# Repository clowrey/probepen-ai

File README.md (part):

# ProbePen-AI

A USB-C pen-shaped two-channel oscilloscope built around an **RP2354B** and an **AD9288** dual 8-bit
ADC, with an IPS LCD on the underside, four side buttons, a 4-channel logic pod and a WAGO push-in
terminal at the nose for the two probe inputs. Everything (schematic, placement, routing,
fabrication files, case and firmware) is generated by scripts in this repository.

> **Status (2026-11-27):** re-laid out and fully routed on the `relayout` branch: KiCad DRC with
> schematic parity reports 0 errors and 0 unconnected items (the only warnings are the open ends of the
> In2 supply rails, by design), ERC is clean and all 149 offline tests pass. 2.5 m of track, 223 vias.
> About 160 mm of slow signals (gain-switch and DC-sense lines, two buttons, pod and LCD control) use
> the inner layers as jumpers, the longest 27 mm. The case fits the routed board, and the firmware
> has its full main loop and user interface (host-tested; not yet built against the Pico SDK).
> No board has been made or bench-tested yet.

**Try it in the browser: [ProbePen-AI simulator](https://clowrey.github.io/probepen-ai/).** The page runs the
firmware's own user interface (`firmware/src`, compiled to WebAssembly) on simulated probe signals. You
can press the side buttons, connect preset signals (UART, PWM, fast edges, glitches, over-range, a 12 V
rail, CAN FD, an SPI bus on the logic pod), and drive it from a host app over the real USB command
protocol: capture once or continuously (with a history to scroll back through), measure, calibrate, decode
UART and CAN FD buses into text, stream continuously (with a USB budget you can set, to see where samples start
to drop), take deep records, and receive ASK snapshots. A selector switches between the 150 MHz firmware and
the 250 MHz overclocked build. The simulated hardware is in [`sim/sim.c`](sim/sim.c). AI mode works only in a
local copy of the page (see [AI mode](#ai-mode)), since it needs an API key on your computer.

| | |
|---|---|
| **MCU** | RP2354B (QFN-80, 0.4 mm pitch): dual Cortex-M33 at 150 MHz (or overclocked to 250 MHz, a build option), 2 MB stacked flash, 12 PIO state machines, on-chip 1.1 V core buck (layout copied from the owner's CellKeeper board), 12 MHz Abracon ABM8-272-T3 crystal (the one Raspberry Pi tuned the Pico 2 for: ESR ≤ 50 Ω, 15 pF load caps, 1 kΩ on XOUT) |
| **Scope ADC** | AD9288 (LQFP-48, hand-soldered, not placed by the assembler): two 8-bit channels, read by one PIO program as one 32-bit word per sample, clocked by PIO side-set at up to 75 MSPS (150 MHz / 2 / integer divider, set by the timebase), or 125 MSPS in the 250 MHz build |
| **Front end** | Per channel: 940 kΩ (2 × 470 kΩ, each bridged by 2.2 pF: 1.1 pF in all, 100 V) into a 100 kΩ / 51 kΩ divider biased from the 3.000 V reference (rests at 0.978 V), BAV199 clamp, RS8752 buffer, RS8752 inverting gain stage pivoting on REF_MID (0.978 V), 74LVC2G66 gain switch. High range about ±5 V, low range about ±26 V |
| **References and supplies** | REF3030 (3.000 V), two RT9013-33 LDOs (`+3V3_DIG`, and `+3V3_ANA` behind a 600 Ω ferrite); the analog ground island joins digital ground at one 0 Ω link (R16) |
| **Logic pod** | 6-pin JST-SH side connector on GPIO0..3 (the 5 V tolerant pins, while the pen is powered), 1 kΩ in each line, PTC-fused 3.3 V out, SRV05-4 ESD with its VP pin open (tied to VBUS, a live target would power the unplugged pen through it) |
| **Display and buttons** | 1.14" 135 × 240 ST7789V IPS LCD (Wisevision N114-2413THBIG01-H13, LCSC C2890618), its 13-pin 0.7 mm flex soldered to pads on the bottom side (SPI1), AO3401A backlight switch; four side-actuated buttons (ASK, MODE/BOOTSEL, UP, DOWN); two front white work-light LEDs |
| **Board** | 132 × 17.6 mm, tapered to 14 mm at the nose, 4 layers (JLC04161H-7628), 1.6 mm, single-sided assembly on the top |
| **Case** | Two-piece build123d pen shell, 136 × 21.5 × 12.2 mm; screws self-tap into the plastic (no inserts) |

## Scope specifications

These figures come from the circuit values, the datasheets and the firmware as it is written today
(`firmware/src/app.c`, `main.c`). No board has been measured yet. Rows marked *possible* need a
firmware change but no hardware change.

| | |
|---|---|
| **Channels** | 2, sampled at the same instant (both AD9288 encode pins are driven from one MCU clock pin) |
| **Resolution** | 8 bits. One step is 39 mV on the ±5 V range and 214 mV on the ±26 V range |
| **Ranges** | ±5.0 V (high gain) and about ±26 V (low gain), chosen per channel, automatically or fixed. Auto-range switches up at 90 % of ±5 V or when the ADC reports over-range, and back down below 70 % |
| **Input** | About 975 kΩ, DC coupled. The divider is compensated: 1.1 pF over 22 pF, plus the clamp, buffer and pads (about 5 pF), plus an optional 2–10 pF trimmer (`CT1`/`CT2`, on the bottom). The trimmer only adds capacitance; fit it and set it for a flat square wave |
| **Bandwidth** | About 25 MHz expected: the 31 MHz anti-alias filter (51 Ω × 100 pF) in front of the ADC together with the gain stage's feedback pole (1.5 kΩ ∥ 2.2 pF, 48 MHz, on the ±5 V range; it was 23 MHz with 4.7 pF). The 250 MHz RS8752 amplifiers are not the limit. Not yet measured |
| **Maximum sample rate** | 75 MS/s on each channel at once (150 MHz system clock ÷ 2 PIO cycles per sample) |
| **Overclocked build** | `cmake -DPROBEPEN_SYS_MHZ=250`: the RP2354B at 250 MHz (core voltage raised to 1.20 V at boot) and the AD9288 at up to **125 MS/s** per channel, beyond the AD9288-80's 80 MS/s rating. Every rate in the firmware follows from the clock (`firmware/include/probepen_clock.h`): sample rates are 125 MHz ÷ an integer, peak detect runs at 4.2 MS/s, and bus decoding gets 5/3 the CPU time. Neither the core, the flash (its clock follows the system clock) nor the ADC has been run this fast on this board; the simulator has a build for each clock |
| **One channel faster?** | Not yet in firmware. Showing one channel does not raise the rate. The board gives channel B its own encode clock pin (GPIO28, `ADC_CLKB`), so a firmware mode can clock the two channels 180° apart and interleave them: **150 MS/s on one signal** (250 MS/s in the 250 MHz build), with both probe tips on the same point. Today the firmware clocks the two channels in phase. Interleaving doubles the sample density, not the bandwidth (the 31 MHz anti-alias filter stays), and needs the two channels' gain, offset and timing matched by calibration |
| **Sample rate per timebase** | At 150 MHz: 100 ns/div to 1 µs/div: 75 MS/s. 2 µs: 25 MS/s. 5 µs: 10.7 MS/s. 10 µs: 5 MS/s. 20 µs: 2.4 MS/s. All rates are 75 MHz ÷ an integer, so there is no clock jitter from fractional dividers |
| **Peak detect** | At 50 µs/div and slower, the ADC keeps running at 2.5 MS/s (4.2 MS/s at 250 MHz). Every 4 to 2048 samples are reduced to a minimum and a maximum, so pulses of 0.4 µs or longer still show at 50 ms/div |
| **Record length (screen)** | 4096 samples per channel per capture (16 KB DMA buffer). Each capture holds about 4 screen widths, used for the trigger search: 512 samples (6.8 µs) at 100 ns/div, 3000 samples (40 µs) at 1 µs/div, about 2000 samples at slower timebases (0.8 ms at 20 µs/div, 0.4 s at 10 ms/div), and 4096 samples (1.7 s) at 50 ms/div |
| **Deep record** | `DEEP n [ch] [rate]`: one long record at 75 MS/s, or 75 MS/s ÷ an integer: **196,608 samples per channel with both channels (2.62 ms at 75 MS/s), or 393,216 with one (5.24 ms)**. Two PIO state machines run in lockstep, one per 8-bit bus, so each sample takes 1 byte (the screen capture spends a 32-bit word per sample pair). The 384 KB buffer is shared with the stream ring, the capture ring and the LCD framebuffer, since only one of them runs at a time. The firmware finds the trigger in the record, then sends it over USB in the stream's CRC-checked blocks: about 0.4 s for a full record at 1 MB/s. `host/probepen.py PORT deep [N] [CH] [RATE] [OUT]` saves it as CSV. Not yet run on a board |
| **Trigger** | Software trigger on the captured record: rising or falling edge, on CH1 or CH2, with 3 codes of hysteresis. The trigger point sits a quarter of the way across the screen, so 25 % of the screen is pre-trigger. If no edge is found, the display free-runs (like *Auto*) and the trigger label turns grey |
| **Trigger level** | Any 8-bit code, 0–255. Holding UP/DOWN moves it 4 codes at a time (157 mV on ±5 V, 0.86 V on ±26 V); the USB command `TRIG n` sets an exact code. It is drawn as a tick on the left edge and shown in volts in the header |
| **Trigger timing** | The trigger lands on the first sample past the level, with no interpolation between samples, so the trace can shift by up to one sample period (13.3 ns at 75 MS/s). Captures are taken back to back, and while a frame is being drawn and sent to the LCD (about 15–20 ms per frame, estimated), new edges are not seen. It is a display trigger, not a hardware trigger that catches every event |
| **Timing accuracy** | Set by the ±30 ppm 12 MHz crystal. The frequency readout averages every crossing in the record, so its error is about one sample period divided by the record's duration |
| **Voltage accuracy** | Offset: `CAL` with both tips on AGND zeroes both ranges of each channel separately, and the result is stored in flash. Gain: uncalibrated, the result depends on 1 % resistors, the 0.2 % REF3030 and the AD9288's own gain error, so expect a few percent. A two-point gain calibration routine exists (`afe_calibrate_two_point`) but no command is wired to it yet. Linearity is about ±½ LSB typical (AD9288 datasheet) |
| **Meter mode** | Two pages in large digits, UP or DOWN to turn. **VOLTS:** per channel the DC level from the RP2354B's 12-bit ADC on each gain stage (`CHx_DC_SENSE`, 10 kΩ / 10 nF), slow but finer than the 8-bit scope ADC, and the AC RMS from the scope capture (over whole periods), with peak to peak beside it. **TIMING:** per channel the frequency, the duty, and the pulse widths, time high (+W) and time low (−W), from a Schmitt trigger centred on the signal's midpoint, so equal rise and fall times cancel. The readings are averaged (time constant 0.8 s), and a change of more than 15 % is shown at once when two readings in a row agree, as on a bench meter. The meter picks its own capture window: it starts at the fastest rate and lengthens the window until it holds 6 to 60 periods, so a slow sample rate cannot report an alias; DC and quiet inputs get the longest window (0.4 s). The timing page works up to about 3.7 MHz (20 samples per period); above that, use the scope. Leaving METER gives the scope its timebase back. The raw readings are also in `MEAS?` as `VRMS= TH= TL= DUTY=` |
| **Logic pod** | 4 inputs (5 V tolerant), sampled at the scope's rate for the timebase, up to 75 MS/s, 4096 samples. Shows each line's level and edge count |
| **USB capture** | Full speed (12 Mbit/s) CDC serial. `CAPTURE n` (up to 4096) or a long press of ASK sends the last capture of both channels as framed binary with a CRC, 16 bits per sample: a full 2 × 4096 record is 16 KB |
| **USB streaming** | `STREAM rate [ch]` sends continuous 8-bit samples until `STREAM 0` or any button: any rate from about 1 S/s to 75 MS/s per channel, CH1, CH2 or both interleaved. The ADC runs at 75 MHz ÷ an integer. Below 1144 S/s the firmware averages several raw samples into each one, which gives less noise and finer resolution. The samples go out in 1 KB blocks with a CRC. Each block carries the index of its first sample, so the host sees exactly how many samples were lost if it falls behind. The pen shows the rate, the USB throughput and any losses on its screen. The USB serial buffer is raised from TinyUSB's 64 bytes to 4 KB for this. **Throughput:** a full-speed link carries at most 1.216 MB/s (19 packets of 64 bytes per millisecond); 0.8–1.1 MB/s is typical in practice. That gives about **1 MS/s on one channel, or 500 kS/s on each of two**, without losses. Faster rates still run, with the gaps marked. Not yet measured on a board; the simulator models the link as 1 MB/s. `host/probepen.py PORT stream RATE [CH] [SECONDS] [OUT]` records a stream and reports what it measured |
| **Continuous capture** | The host asks for the next capture (`CAPTURE n`) as soon as one arrives: a series of triggered captures, each with its measurements. The simulator's *Continuous* box keeps the last 200 with a slider to look back through them; `host/probepen.py PORT watch [N] [COUNT] [OUT.jsonl]` prints each one and logs it |
| **Bus decoding** | `DECODE UART src baud` or `DECODE CAN src rate [data_rate]`: the pen decodes UART and CAN / CAN FD from CH1, CH2 or CH1 − CH2 and sends only the result, one text line per UART line or CAN frame, and shows it on its screen. See [Decoding protocols on the pen](#decoding-protocols-on-the-pen) |

## Decoding protocols on the pen

Streaming raw samples is limited by USB to about 1 MB/s. Decoding a bus on the pen sends only the
result: CAN frames, I²C transactions or UART bytes are a few kilobytes per second even on a busy bus.
The firmware is open and built for this kind of change. The user interface, capture processing and
streaming are plain C that compiles and is tested on a PC. A new decoder is a small module of the
same kind: samples in, decoded messages out. It can be tested on recorded or synthetic signals, run
in the [web simulator](https://clowrey.github.io/probepen-ai/), then flashed by drag-and-drop
(hold MODE/BOOTSEL while plugging in). UART and CAN / CAN FD are done ([`decode.c`](firmware/src/decode.c),
below); the table after that sets out what the hardware allows for the rest.

**What exists: `DECODE`.**
- `DECODE UART src baud`, `DECODE CAN src rate [data_rate]`, `DECODE 0` (or any button) to stop; src 1 = CH1,
  2 = CH2, 3 = CH1 − CH2 (CAN_H − CAN_L, as a transceiver sees it). The reply gives the plan:
  `OK PROTO= SRC= RATE= DATA= FS= DIV= SPB= MODE=LIVE|BURST COVER= BURSTN=`. Then one line per UART line
  (or 64 bytes) or per CAN frame: `DEC UART T=<s> BYTES= FE=<framing errors> HEX=…` and
  `DEC CAN T=<s> ID= EXT= FD= BRS= ESI= RTR= DLC= LEN= ACK= ERR=NONE|STUFF|CRC|SC|FORM HEX=…`, and
  `DECODE END RECORDS= ERRORS= LOST= SAMPLES=` at the stop. The pen's screen shows the decoded text.
- The ADC runs at 8 samples per bit of the fastest phase (4 when that would pass 18.75 MS/s). Two thresholds
  follow the signal's own high and low levels, so no level needs setting (the swing must be at least 12 codes:
  0.47 V on the ±5 V range, 2.6 V on ±26 V), and the first long quiet run tells which level is idle (a TTL
  UART idles high, CAN_H and CH1 − CH2 idle low). Only edges cost real work: the time between two edges gives
  a whole number of bits, and the bit clock re-locks on every edge.
- UART: 8N1, either polarity. CAN: classic and FD, base and extended IDs, destuffing, the bit-rate switch (at
  the BRS bit's sample point), the FD stuff count, and the CRC (15, 17 or 21 bits) checked; the ACK slot is
  reported. The CRC and stuffing rules are from ISO 11898-1 as written in the code and agree with two
  encoders written separately (`sim/sim.c`, `tests/test_decode.py`); they have not yet met a real CAN
  controller.
- **Live** when the sample rate is at most 10 MS/s at 150 MHz (16.7 MS/s at 250 MHz; an estimate of what one
  core keeps up with, to be measured): every sample is decoded, without gaps. That covers UART to about
  1.2 Mbaud, and classic CAN and CAN FD without a bit-rate switch to 1 Mbit/s. **Burst** above that: the pen
  records 320 k samples at full rate, decodes them, and records again, so some frames are missed. CAN FD at
  500 k / 2 Mbit/s samples at 18.75 MS/s in bursts of 8.7 ms and sees about 44 % of the time (58 % at 250 MHz).
- **On the pen alone:** DECODE is the last mode on the MODE button. UP and DOWN pick the bus, ASK holds,
  and the decoded text scrolls on the screen. *UART auto* listens at 8.3 MS/s, takes the shortest pulse as one
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
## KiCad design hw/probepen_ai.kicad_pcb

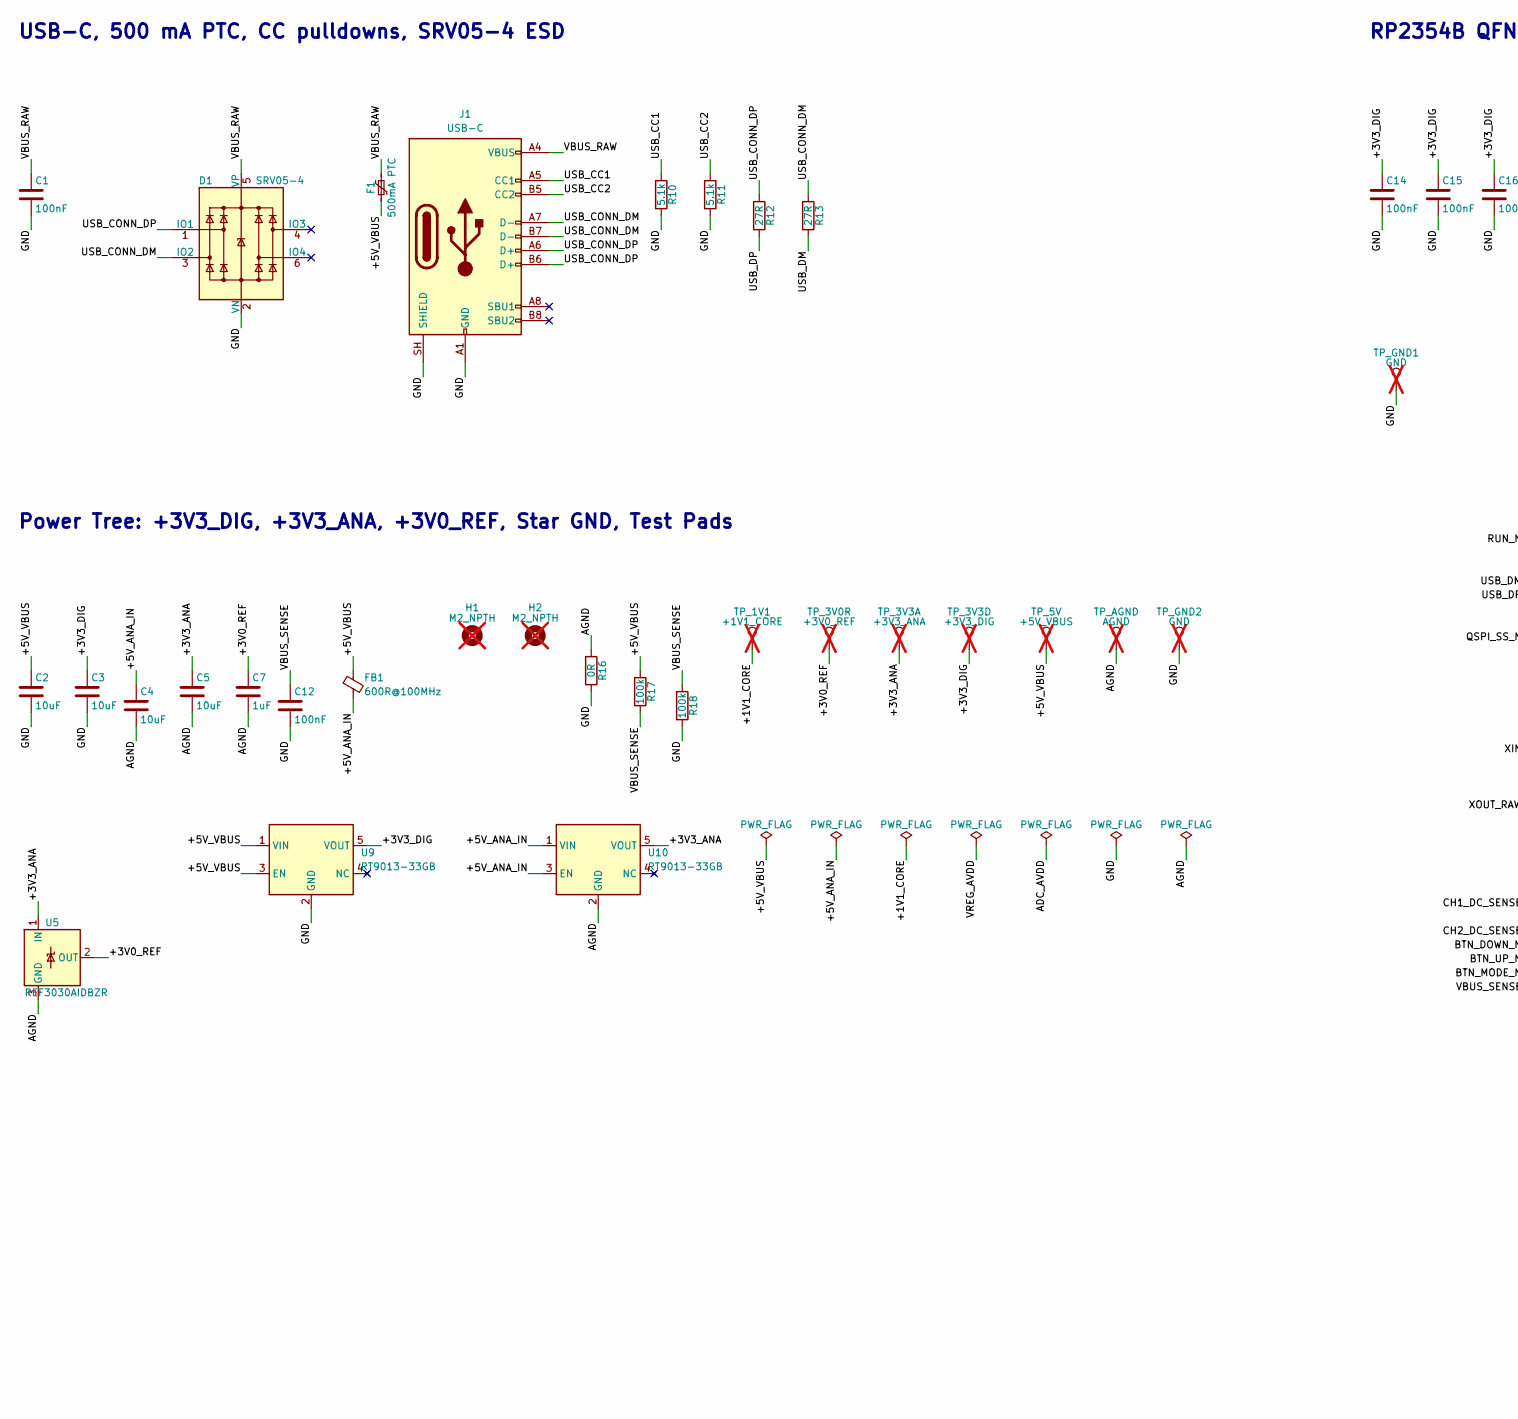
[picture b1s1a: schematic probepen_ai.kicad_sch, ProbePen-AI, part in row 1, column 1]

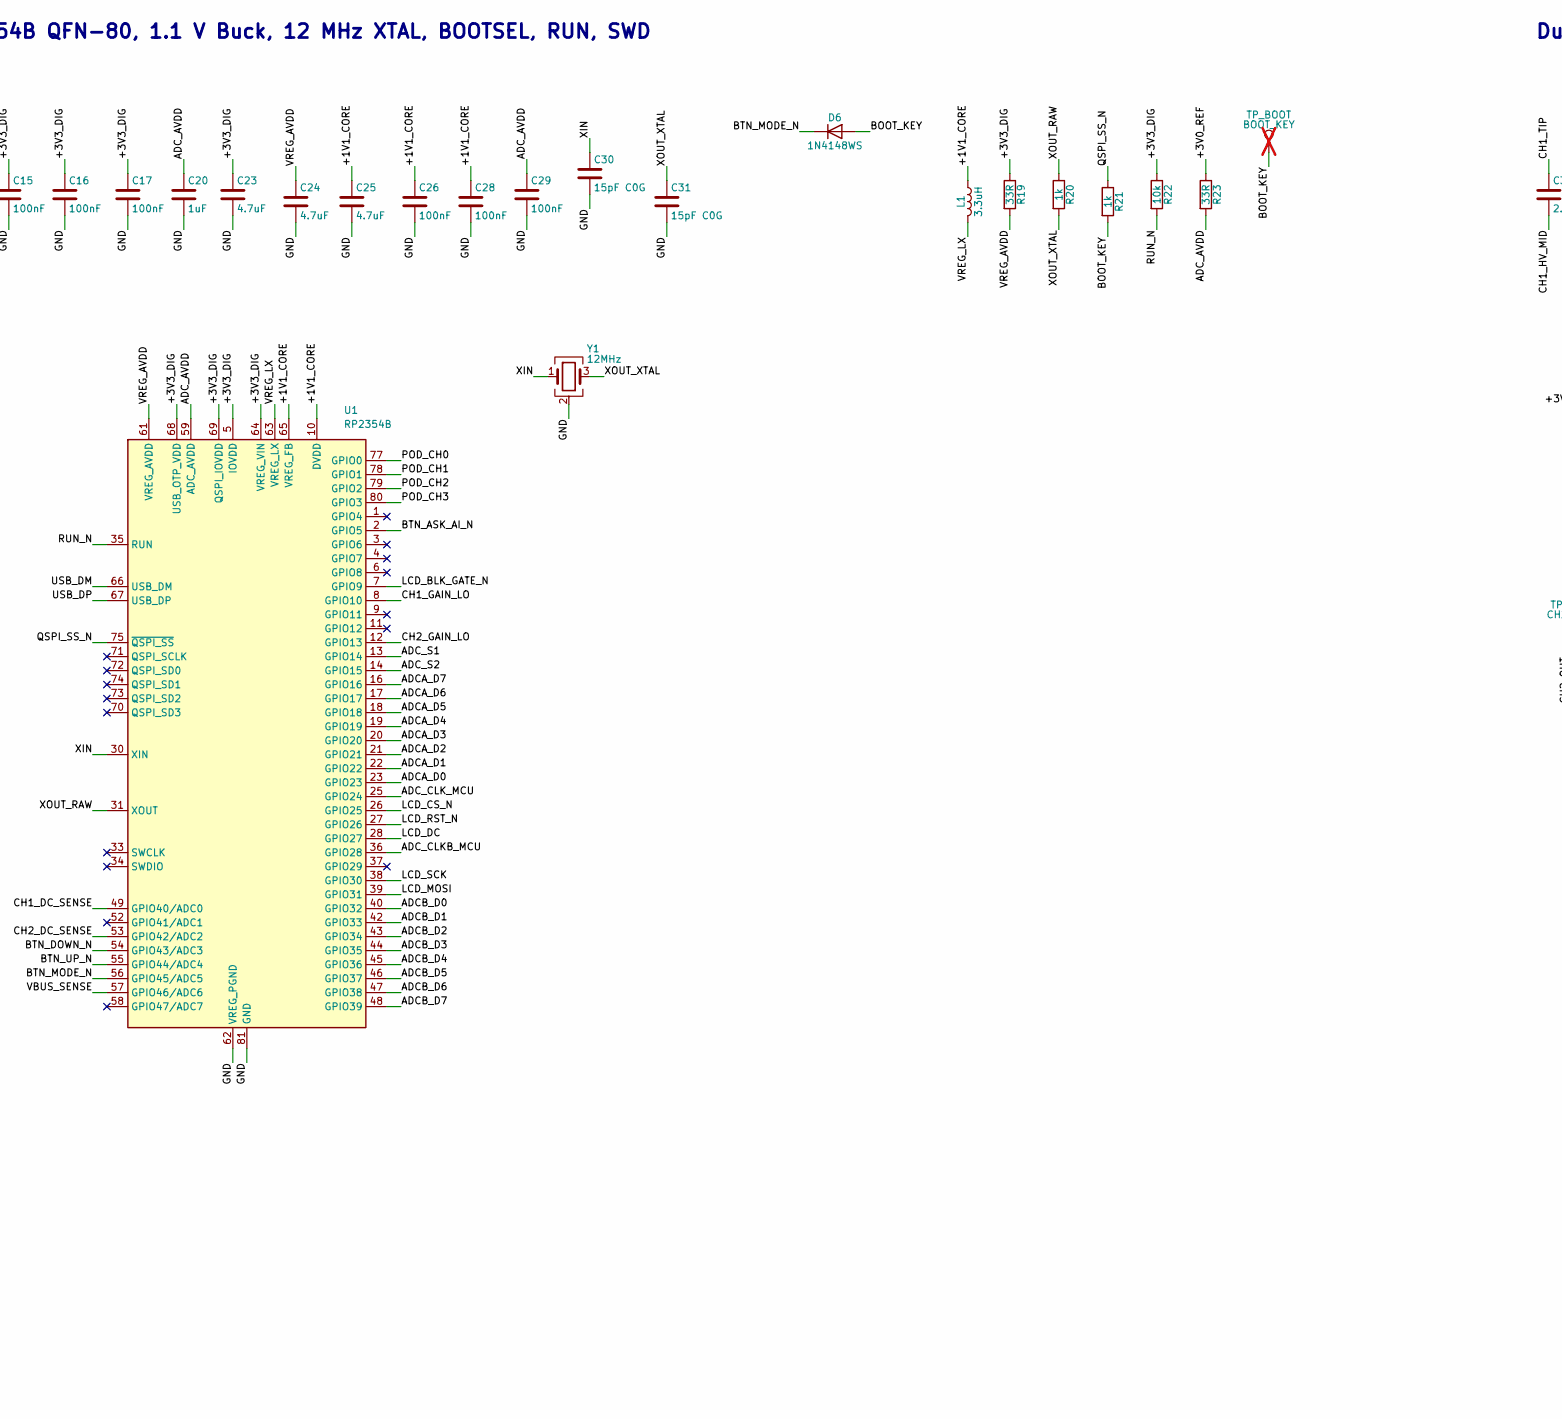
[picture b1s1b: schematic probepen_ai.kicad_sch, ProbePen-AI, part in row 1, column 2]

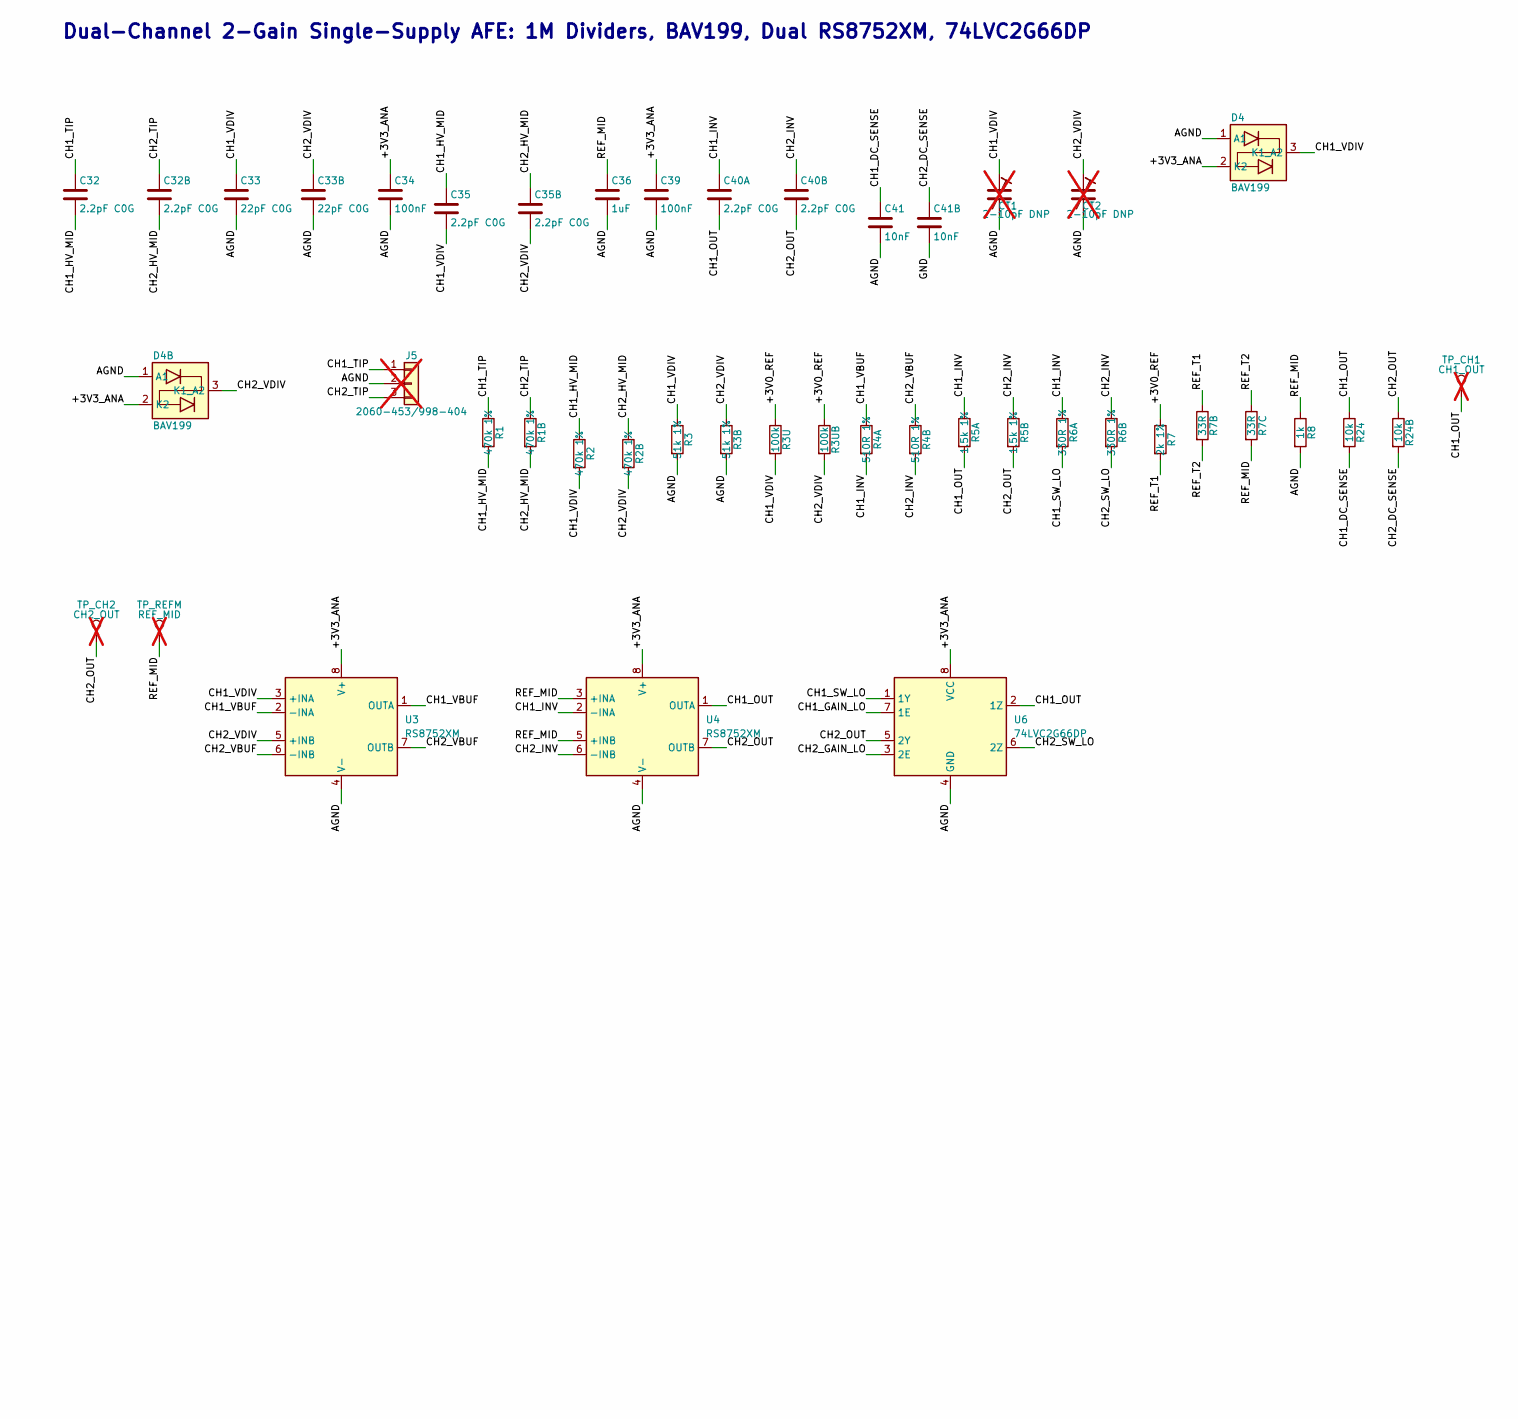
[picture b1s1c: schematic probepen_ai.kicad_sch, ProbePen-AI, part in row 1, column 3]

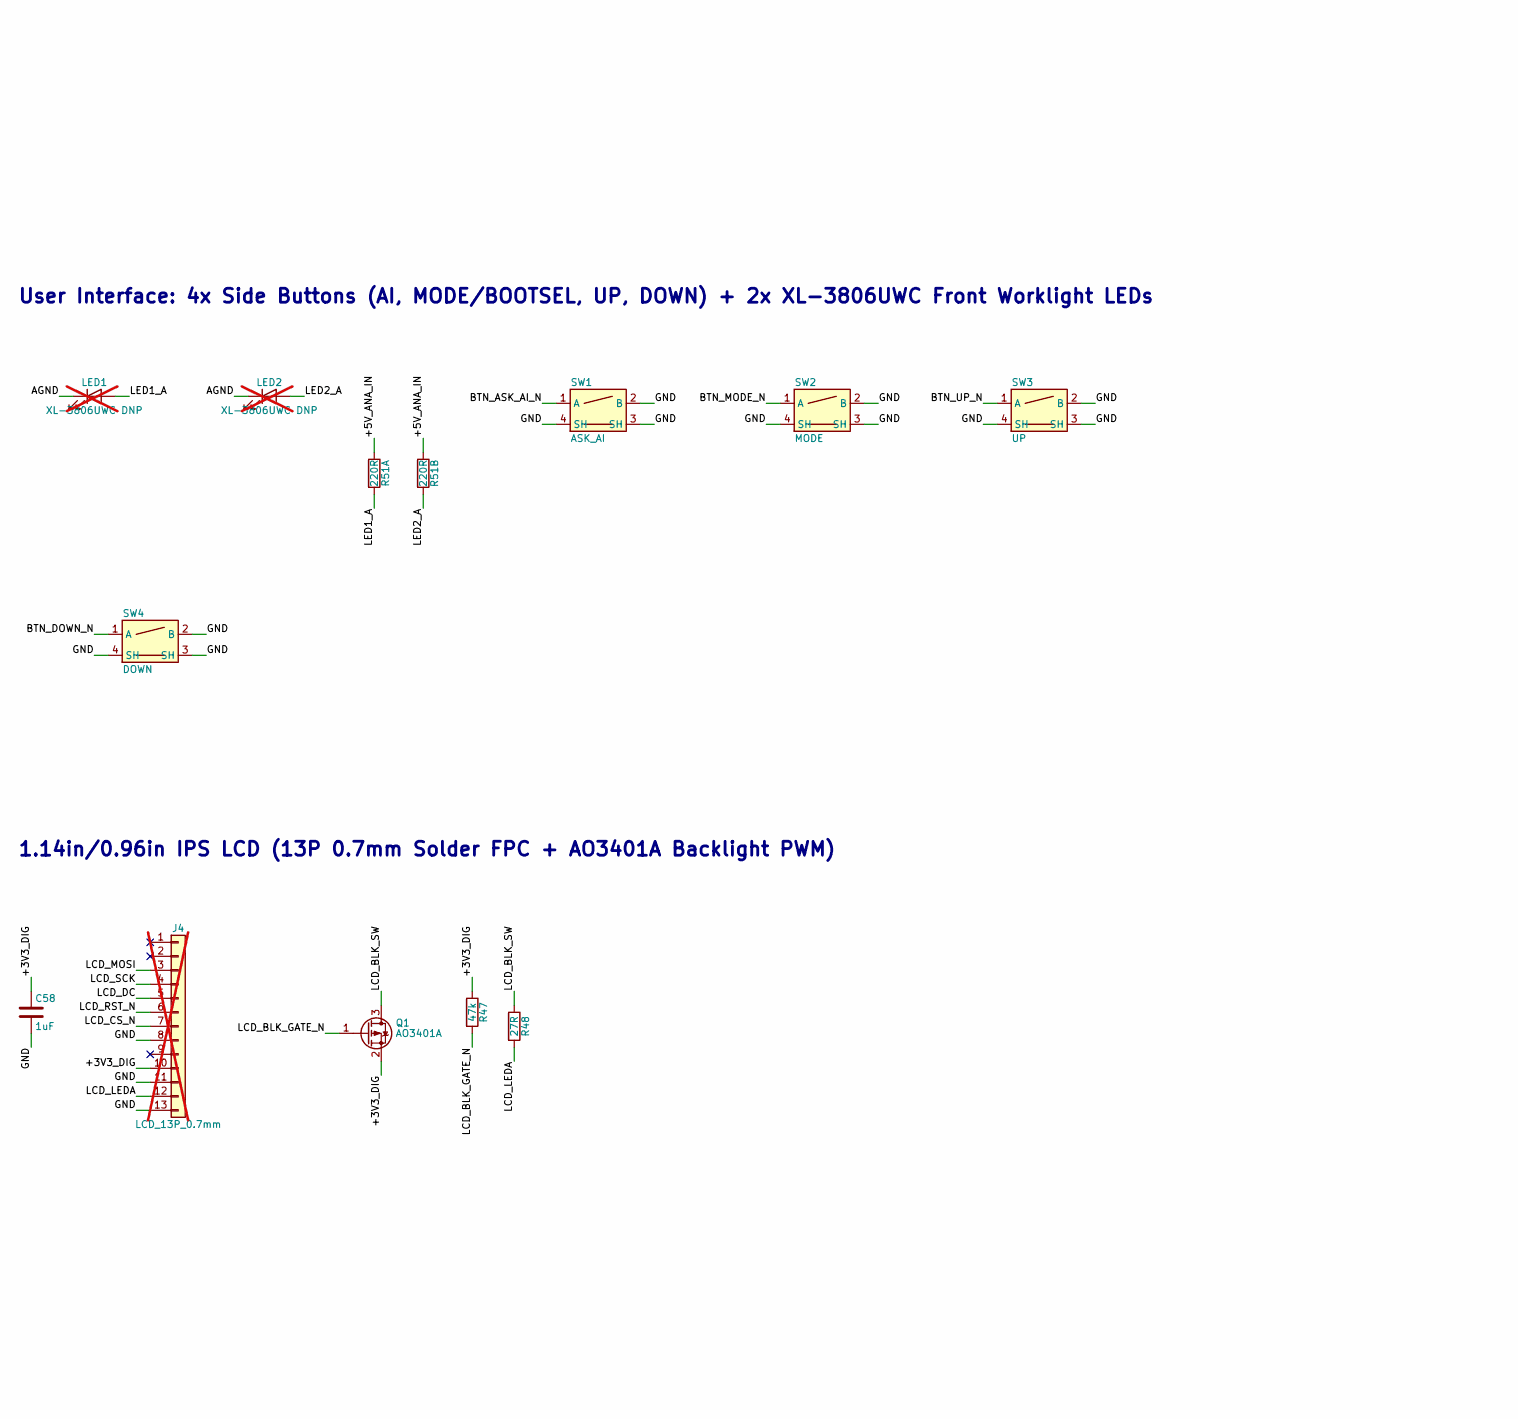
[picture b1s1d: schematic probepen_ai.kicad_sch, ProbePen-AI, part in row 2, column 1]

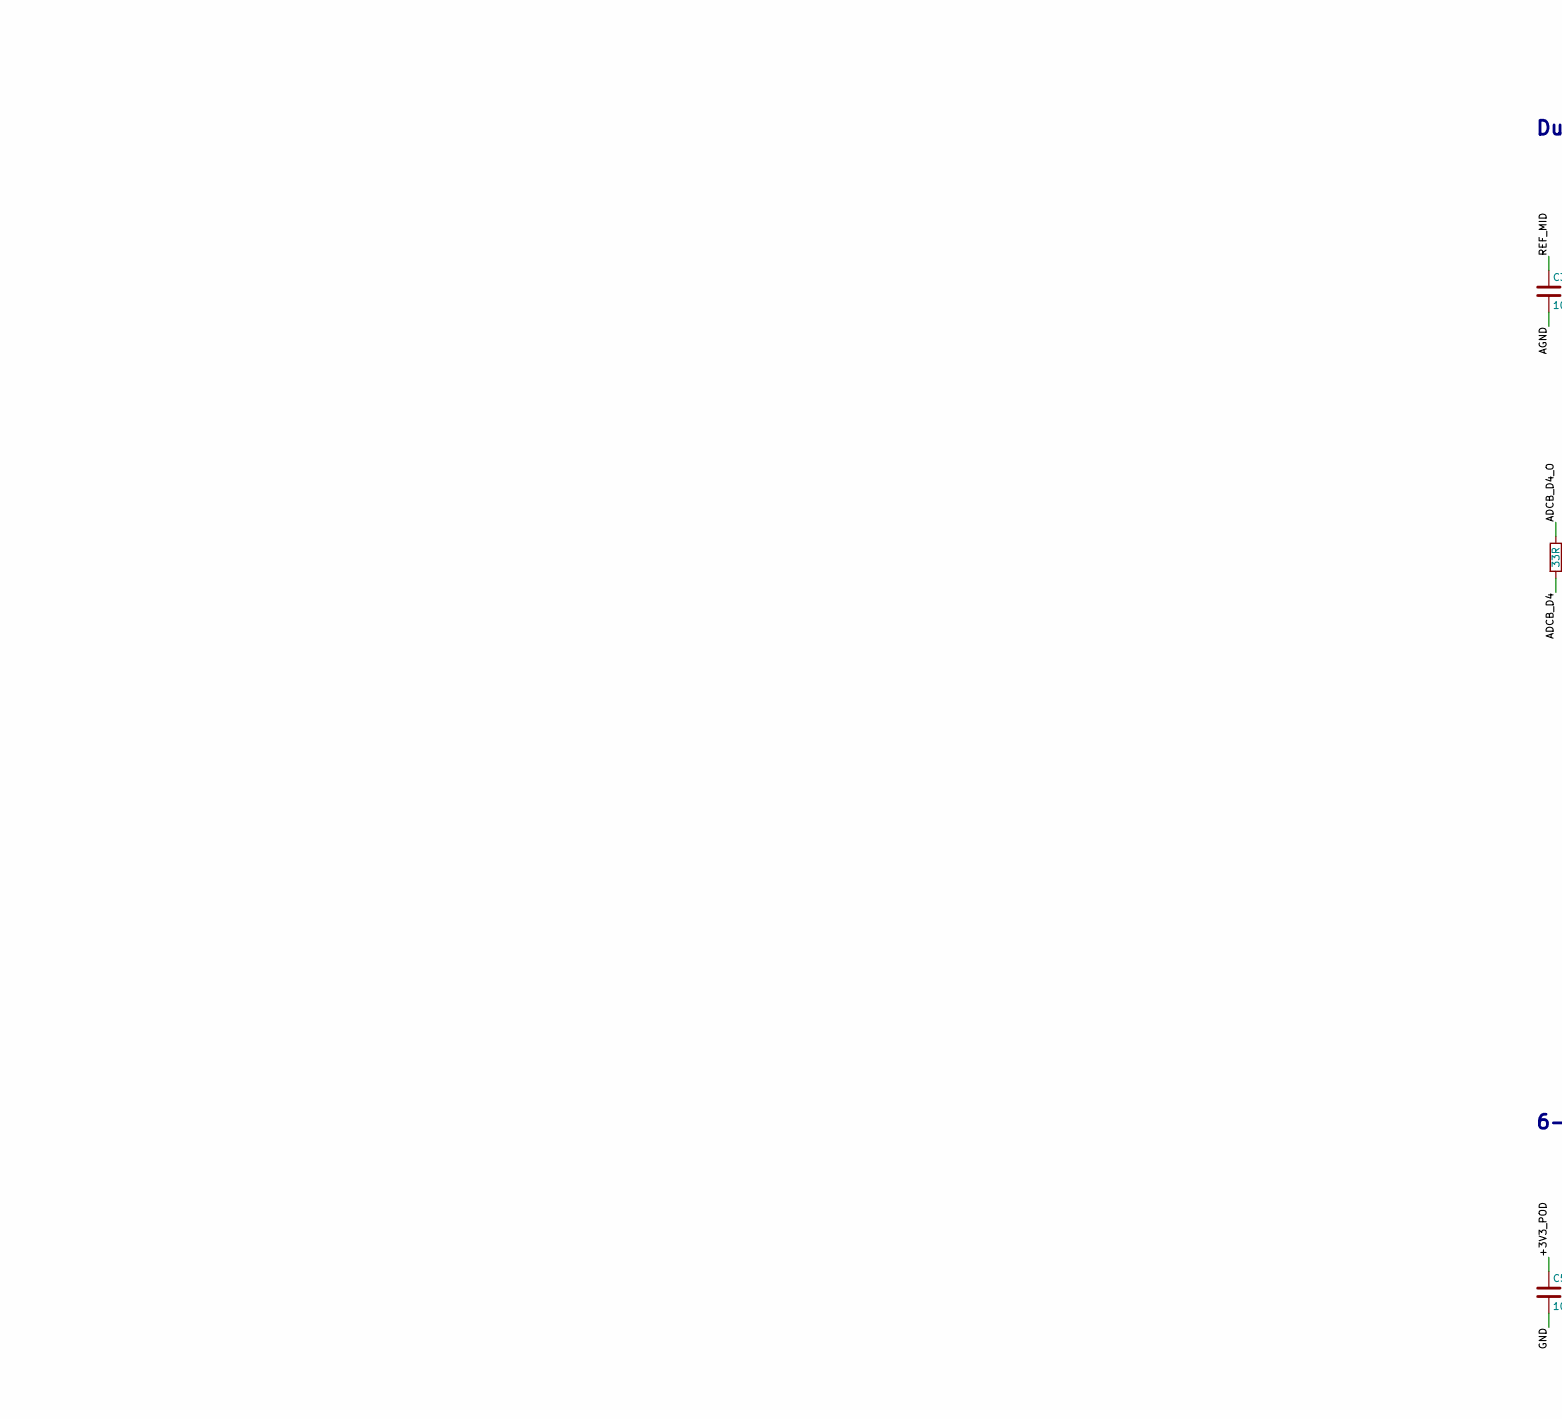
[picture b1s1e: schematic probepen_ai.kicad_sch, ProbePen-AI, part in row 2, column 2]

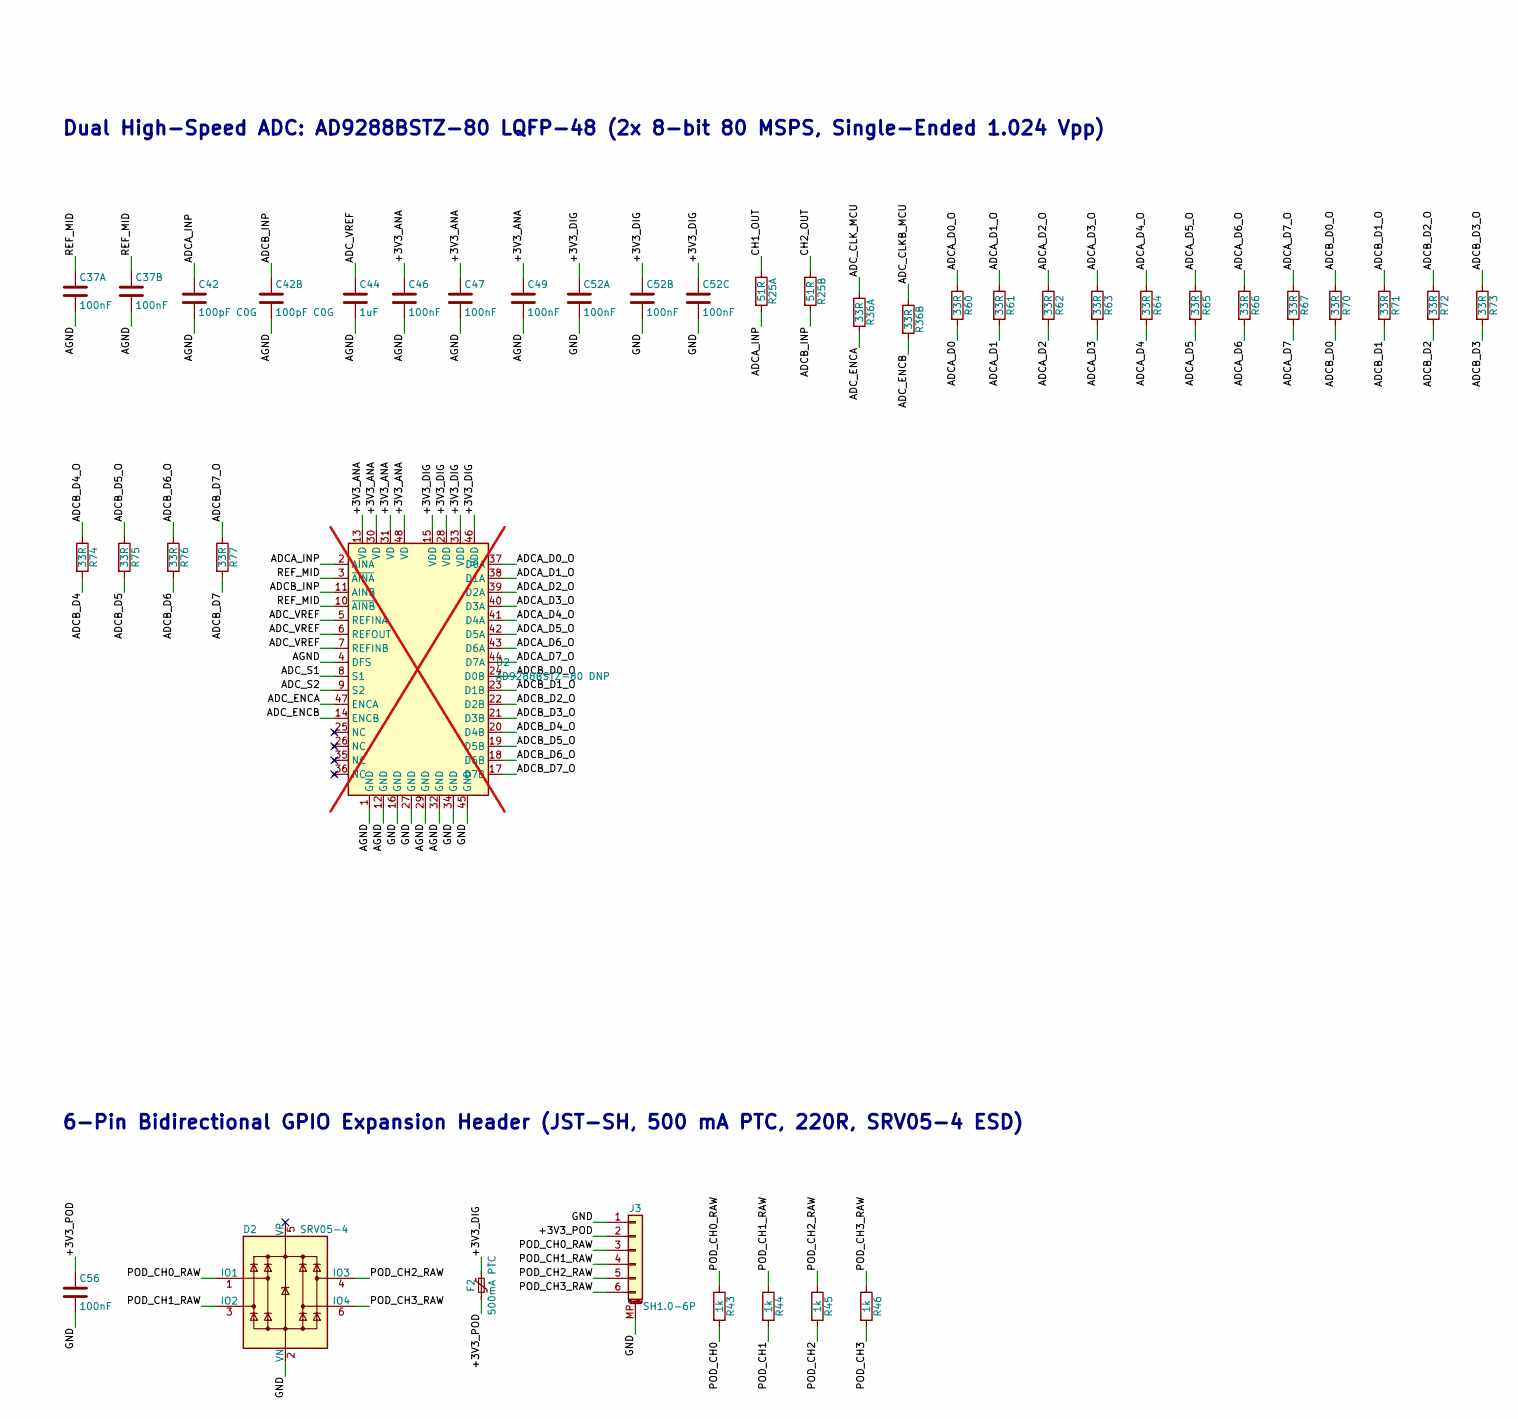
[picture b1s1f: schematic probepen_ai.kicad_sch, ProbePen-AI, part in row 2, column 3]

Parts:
C1, C12, C14, C15, C16, C17, C26, C28, C29, C34, C37A, C37B, C39, C46, C47, C49, C52A, C52B, C52C, C56: 100nF; C_0402_1005Metric; MPN CL05B104KO5NNNC; LCSC C1525
C2, C3, C4, C5: 10uF; C_0603_1608Metric; MPN CL10A106KP8NNNC; LCSC C19702
C7, C20, C36, C44, C58: 1uF; C_0402_1005Metric; MPN CL05A105KA5NQNC; LCSC C52923
C23, C24, C25: 4.7uF; RP2350_80QFN_minimal__C_0402_1005Metric_small_pads; MPN CL05A475MP5NRNC; LCSC C23733
C30, C31: 15pF C0G; C_0402_1005Metric; MPN 0402CG150J500NT; LCSC C1548
C32, C32B, C35, C35B, C40A, C40B: 2.2pF C0G; C_0402_1005Metric; MPN 0402CG2R2C500NT; LCSC C1559
C33, C33B: 22pF C0G; C_0402_1005Metric; MPN 0402CG220J500NT; LCSC C1555
C41, C41B: 10nF; C_0402_1005Metric; MPN CL05B103KB5NNNC; LCSC C15195
C42, C42B: 100pF C0G; C_0402_1005Metric; MPN 0402CG101J500NT; LCSC C1546
CT1, CT2: 2-10pF DNP; C_Trimmer_Knowles_JZ100_4.5x3.2mm; not fitted
D1, D2: SRV05-4; SOT-23-6; MPN SRV05-4; LCSC C7420376
D4, D4B: BAV199; SOT-23; MPN BAV199,215; LCSC C40919
D6: 1N4148WS; D_SOD-323; MPN 1N4148WS; LCSC C2128
F1, F2: 500mA PTC; Fuse_0805_2012Metric; MPN SMD0805P050TF; LCSC C20978
FB1: 600R@100MHz; L_0603_1608Metric; MPN GZ1608D601TF; LCSC C1002
H1, H2: M2_NPTH; MountingHole_2.2mm_M2; not fitted
J1: USB-C; USB_C_Receptacle_HRO_TYPE-C-31-M-12; MPN TYPE-C-31-M-12; LCSC C165948
J3: SH1.0-6P; JST_SH_SM06B-SRSS-TB_1x06-1MP_P1.00mm_Horizontal; MPN HC-SH1.0-6PWT; LCSC C53454624
J4: LCD_13P_0.7mm; LCD_FPC_13P_P0.70mm_Solder; not fitted
J5: 2060-453/998-404; Nose_WAGO2060_KF381_ProbePads; MPN 2060-453/998-404; LCSC C2765056; not fitted
L1: 3.3uH; RP2350_80QFN_minimal__L_pol_2016; MPN AOTA-B201610S3R3-101-T; LCSC C42411119
LED1, LED2: XL-3806UWC DNP; LED_Side_XL3806_3.8x1.0mm; not fitted
Q1: AO3401A; SOT-23; MPN AO3401A; LCSC C15127
R1, R1B, R2, R2B: 470k 1%; R_0805_2012Metric; MPN 0805W8F4703T5E; LCSC C17709
R3, R3B: 51k 1%; R_0402_1005Metric; MPN 0402WGF5102TCE; LCSC C25794
R3U, R3UB, R17, R18: 100k; R_0402_1005Metric; MPN 0402WGF1003TCE; LCSC C25741
R4A, R4B: 510R 1%; R_0402_1005Metric; MPN 0402WGF5100TCE; LCSC C25123
R5A, R5B: 1.5k 1%; R_0402_1005Metric; MPN 0402WGF1501TCE; LCSC C25867
R6A, R6B: 330R 1%; R_0402_1005Metric; MPN 0402WGF3300TCE; LCSC C25104
R7: 2k 1%; R_0402_1005Metric; MPN 0402WGF2001TCE; LCSC C4109
R7B, R7C, R19, R23, R36A, R36B, R60, R61, R62, R63, R64, R65, R66, R67, R70, R71, R72, R73, R74, R75, R76, R77: 33R; R_0402_1005Metric; MPN 0402WGF330JTCE; LCSC C25105
R8, R20, R21, R43, R44, R45, R46: 1k; R_0402_1005Metric; MPN 0402WGF1001TCE; LCSC C11702
R10, R11: 5.1k; R_0402_1005Metric; MPN 0402WGF5101TCE; LCSC C25905
R12, R13, R48: 27R; R_0603_1608Metric; MPN 0603WAF270JT5E; LCSC C25190
R16: 0R; R_0603_1608Metric; MPN 0603WAF0000T5E; LCSC C21189
R22, R24, R24B: 10k; R_0402_1005Metric; MPN 0402WGF1002TCE; LCSC C25744
R25A, R25B: 51R; R_0402_1005Metric; MPN 0402WGF510JTCE; LCSC C25125
R47: 47k; R_0402_1005Metric; MPN 0402WGF4702TCE; LCSC C25792
R51A, R51B: 220R; R_0402_1005Metric; MPN 0402WGF2200TCE; LCSC C25091
SW1: ASK_AI; SW_Push_Side_TS24CA; MPN TS24CA; LCSC C393942
SW2: MODE; SW_Push_Side_TS24CA; MPN TS24CA; LCSC C393942
SW3: UP; SW_Push_Side_TS24CA; MPN TS24CA; LCSC C393942
SW4: DOWN; SW_Push_Side_TS24CA; MPN TS24CA; LCSC C393942
TP_1V1: +1V1_CORE; TestPoint_Pad_D1.0mm; not fitted
TP_3V0R: +3V0_REF; TestPoint_Pad_D1.0mm; not fitted
TP_3V3A: +3V3_ANA; TestPoint_Pad_D1.0mm; not fitted
TP_3V3D: +3V3_DIG; TestPoint_Pad_D1.0mm; not fitted
TP_5V: +5V_VBUS; TestPoint_Pad_D1.0mm; not fitted
TP_AGND: AGND; TestPoint_Pad_D1.0mm; not fitted
TP_BOOT: BOOT_KEY; TestPoint_Pad_D1.0mm; not fitted
TP_CH1: CH1_OUT; TestPoint_Pad_D1.0mm; not fitted
TP_CH2: CH2_OUT; TestPoint_Pad_D1.0mm; not fitted
TP_GND1, TP_GND2: GND; TestPoint_Pad_D1.0mm; not fitted
TP_REFM: REF_MID; TestPoint_Pad_D1.0mm; not fitted
U1: RP2354B; RP2350_80QFN_minimal__RP2350-QFN-80-1EP_10x10_P0.4mm_EP3.4x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; MPN RP2354B; LCSC C39843328
U2: AD9288BSTZ-80 DNP; LQFP-48_7x7mm_P0.5mm; not fitted
U3, U4: RS8752XM; MSOP-8_3x3mm_P0.65mm; MPN RS8752XM; LCSC C255421
U5: REF3030AIDBZR; SOT-23; MPN REF3030AIDBZR; LCSC C38423
U6: 74LVC2G66DP; TSSOP-8_3x3mm_P0.65mm; MPN 74LVC2G66DP,125; LCSC C282354
U9, U10: RT9013-33GB; SOT-23-5; MPN RT9013-33GB; LCSC C47773
Y1: 12MHz; Crystal_SMD_3225-4Pin_3.2x2.5mm; MPN ABM8-272-T3; LCSC C20625731

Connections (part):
/+1V1_CORE: C25.1, C26.1, C28.1, L1.1, TP_1V1.1, U1.10 (DVDD), U1.32 (DVDD), U1.51 (DVDD), U1.65 (VREG_FB)
/+3V0_REF: C7.1, R3U.1, R3UB.1, R7.1, R23.1, TP_3V0R.1, U5.2 (OUT)
/+3V3_ANA: C5.1, C34.1, C39.1, C46.1, C47.1, C49.1, D4.2 (K2), D4B.2 (K2), TP_3V3A.1, U2.13 (VD), U2.30 (VD), U2.31 (VD), U2.48 (VD), U3.8 (V+), U4.8 (V+), U5.1 (IN), U6.8 (VCC), U10.5 (VOUT)
/+3V3_DIG: C3.1, C14.1, C15.1, C16.1, C17.1, C23.1, C52A.1, C52B.1, C52C.1, C58.1, F2.1, J4.10, Q1.2 (S), R19.1, R22.1, R47.1, TP_3V3D.1, U1.5 (IOVDD), U1.15 (IOVDD), U1.24 (IOVDD), U1.29 (IOVDD), U1.41 (IOVDD), U1.50 (IOVDD), U1.60 (IOVDD), U1.64 (VREG_VIN), U1.68 (USB_OTP_VDD), U1.69 (QSPI_IOVDD), U1.76 (IOVDD), U2.15 (VDD), U2.28 (VDD), U2.33 (VDD), U2.46 (VDD), U9.5 (VOUT)
/+3V3_POD: C56.1, F2.2, J3.2
/+5V_ANA_IN: C4.1, FB1.2, R51A.1, R51B.1, U10.1 (VIN), U10.3 (EN)
/+5V_VBUS: C2.1, F1.2, FB1.1, R17.1, TP_5V.1, U9.1 (VIN), U9.3 (EN)
/ADCA_D0: R60.2, U1.23 (GPIO23)
/ADCA_D0_O: R60.1, U2.37 (D0A)
/ADCA_D1: R61.2, U1.22 (GPIO22)
/ADCA_D1_O: R61.1, U2.38 (D1A)
/ADCA_D2: R62.2, U1.21 (GPIO21)
/ADCA_D2_O: R62.1, U2.39 (D2A)
/ADCA_D3: R63.2, U1.20 (GPIO20)
/ADCA_D3_O: R63.1, U2.40 (D3A)
/ADCA_D4: R64.2, U1.19 (GPIO19)
/ADCA_D4_O: R64.1, U2.41 (D4A)
/ADCA_D5: R65.2, U1.18 (GPIO18)
/ADCA_D5_O: R65.1, U2.42 (D5A)
/ADCA_D6: R66.2, U1.17 (GPIO17)
/ADCA_D6_O: R66.1, U2.43 (D6A)
/ADCA_D7: R67.2, U1.16 (GPIO16)
/ADCA_D7_O: R67.1, U2.44 (D7A)
/ADCA_INP: C42.1, R25A.2, U2.2 (AINA)
/ADCB_D0: R70.2, U1.40 (GPIO32)
/ADCB_D0_O: R70.1, U2.24 (D0B)
/ADCB_D1: R71.2, U1.42 (GPIO33)
/ADCB_D1_O: R71.1, U2.23 (D1B)
/ADCB_D2: R72.2, U1.43 (GPIO34)
/ADCB_D2_O: R72.1, U2.22 (D2B)
/ADCB_D3: R73.2, U1.44 (GPIO35)
/ADCB_D3_O: R73.1, U2.21 (D3B)
/ADCB_D4: R74.2, U1.45 (GPIO36)
/ADCB_D4_O: R74.1, U2.20 (D4B)
/ADCB_D5: R75.2, U1.46 (GPIO37)
/ADCB_D5_O: R75.1, U2.19 (D5B)
/ADCB_D6: R76.2, U1.47 (GPIO38)
/ADCB_D6_O: R76.1, U2.18 (D6B)
/ADCB_D7: R77.2, U1.48 (GPIO39)
/ADCB_D7_O: R77.1, U2.17 (D7B)
/ADCB_INP: C42B.1, R25B.2, U2.11 (AINB)
/ADC_AVDD: C20.1, C29.1, R23.2, U1.59 (ADC_AVDD)
/ADC_CLKB_MCU: R36B.1, U1.36 (GPIO28)
/ADC_CLK_MCU: R36A.1, U1.25 (GPIO24)
/ADC_ENCA: R36A.2, U2.47 (ENCA)
/ADC_ENCB: R36B.2, U2.14 (ENCB)
/ADC_S1: U1.13 (GPIO14), U2.8 (S1)
/ADC_S2: U1.14 (GPIO15), U2.9 (S2)
/ADC_VREF: C44.1, U2.5 (REFINA), U2.6 (REFOUT), U2.7 (REFINB)
/AGND: C4.2, C5.2, C7.2, C33.2, C33B.2, C34.2, C36.2, C37A.2, C37B.2, C39.2, C41.2, C42.2, C42B.2, C44.2, C46.2, C47.2, C49.2, CT1.2, CT2.2, D4.1 (A1), D4B.1 (A1), J5.2, LED1.1 (K), LED2.1 (K), R3.2, R3B.2, R8.2, R16.1, TP_AGND.1, U2.1 (GND), U2.4 (DFS), U2.12 (GND), U2.29 (GND), U2.32 (GND), U3.4 (V-), U4.4 (V-), U5.3 (GND), U6.4 (GND), U10.2 (GND)
/BOOT_KEY: D6.2 (A), R21.2, TP_BOOT.1
/BTN_ASK_AI_N: SW1.1 (A), U1.2 (GPIO5)
/BTN_DOWN_N: SW4.1 (A), U1.54 (GPIO43/ADC3)
/BTN_MODE_N: D6.1 (K), SW2.1 (A), U1.56 (GPIO45/ADC5)
/BTN_UP_N: SW3.1 (A), U1.55 (GPIO44/ADC4)
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
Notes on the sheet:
USB-C, 500 mA PTC, CC pulldowns, SRV05-4 ESD
Power Tree: +3V3_DIG, +3V3_ANA, +3V0_REF, Star GND, Test Pads
User Interface: 4x Side Buttons (AI, MODE/BOOTSEL, UP, DOWN) + 2x XL-3806UWC Front Worklight LEDs
1.14in/0.96in IPS LCD (13P 0.7mm Solder FPC + AO3401A Backlight PWM)
RP2354B QFN-80, 1.1 V Buck, 12 MHz XTAL, BOOTSEL, RUN, SWD
Dual-Channel 2-Gain Single-Supply AFE: 1M Dividers, BAV199, Dual RS8752XM, 74LVC2G66DP
Dual High-Speed ADC: AD9288BSTZ-80 LQFP-48 (2x 8-bit 80 MSPS, Single-Ended 1.024 Vpp)
6-Pin Bidirectional GPIO Expansion Header (JST-SH, 500 mA PTC, 220R, SRV05-4 ESD)

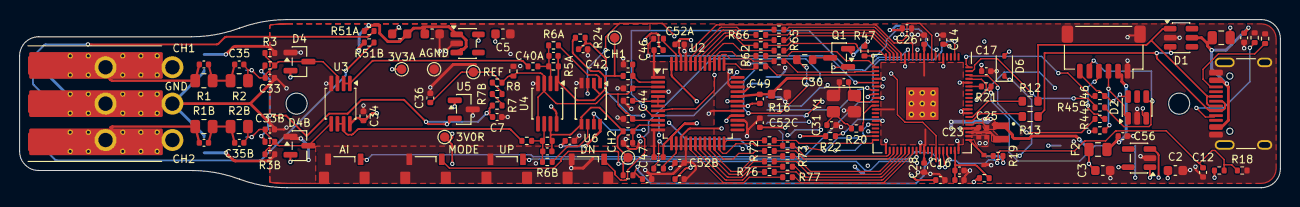
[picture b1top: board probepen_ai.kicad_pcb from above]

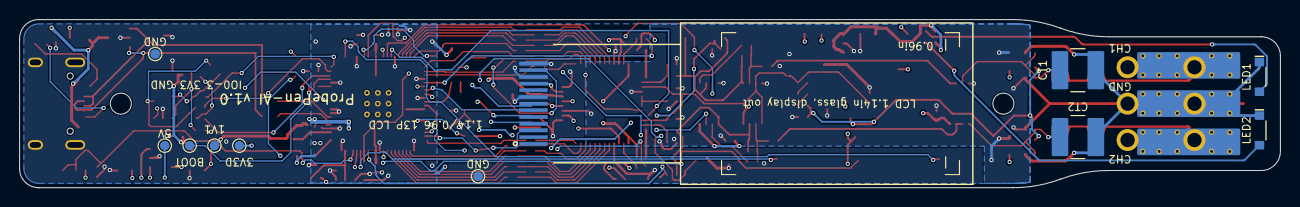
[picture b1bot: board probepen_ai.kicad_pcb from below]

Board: 4 copper layers, 132.0 x 17.6 mm, 151 parts (11 on the bottom side), 110 nets.

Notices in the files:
README.md:
Licence:
GPL-3.0: hardware design files, CAD, firmware and scripts alike. See [LICENSE](LICENSE).
